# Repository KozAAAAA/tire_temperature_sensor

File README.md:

# Tire Temperature Sensor v2.0

**TTS** (Tire Temperature Sensor) is a PCB designed to measure temperature quickly, at a distance, and without the need to touch the wheels. The 4x16 pixel IR camera is used to obtain the data. It communicates with the STM microprocessor via the I2C protocol. Data is then averaged out to a 1x8 array of unsigned ints and sent with the CAN Transceiver to the car’s CAN network. This array can be then read off of the telemetry system implemented in the PM-08 racing car.

## Applications

While driving, a tire heats up. Heat dissipates differently across its surface and its rate changes depending on many factors (E.g. weather conditions or reoccurring acceleration). As a tire has its maximal temperature, exceeding this value may weaken its structural strength and cause its destruction in the worst-case scenario. This IR Camera PCB makes it possible to monitor a tire across its whole surface and prevent any damage associated with the temperature. As TTS monitors every wheel out of 4, our crew can easily detect if tires wear unevenly or excessively. Tire temperature patterns inform whether the car is properly calibrated, as the out-of-tune suspension causes tires to heat up significantly faster. This may result in grip loss in these areas.

## Core features

* 4x16 pixel MLX90621 thermal camera
* STM32L4P5RET
* 24V to 3.3V buck converter
* 3.3V to 2.6V LDO
* 3.3V CAN transceiver
* Overcurrent and reverse polarity protection
* Status LEDs

## PCB

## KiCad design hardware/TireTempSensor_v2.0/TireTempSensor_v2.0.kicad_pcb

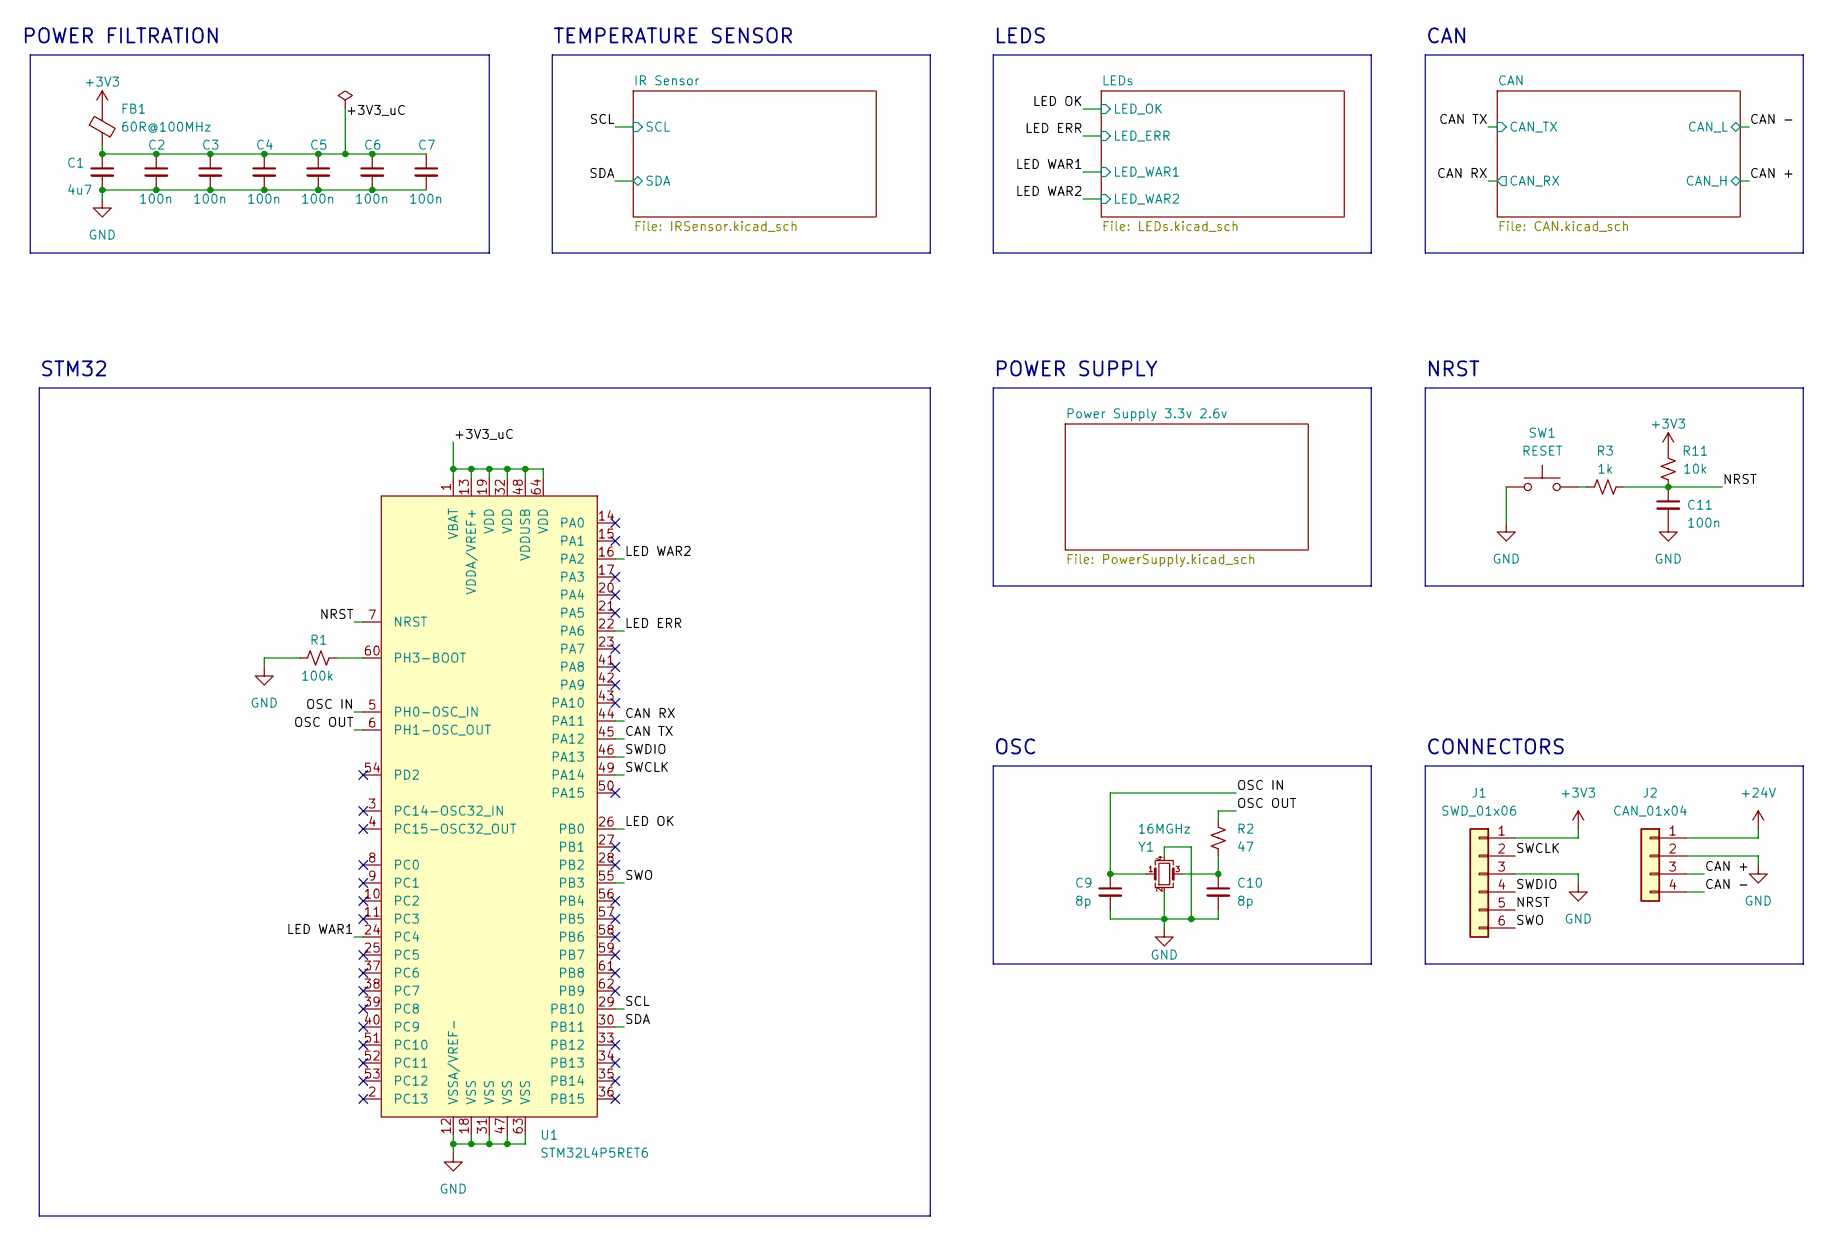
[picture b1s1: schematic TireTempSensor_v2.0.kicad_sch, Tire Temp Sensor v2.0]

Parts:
C1: 4u7; C_0603_1608Metric
C2, C3, C4, C5, C6, C7, C11: 100n; C_0603_1608Metric
C9, C10: 8p; C_0603_1608Metric
FB1: 60R@100MHz; L_0603_1608Metric
J1: SWD_01x06; PinHeader_1x06_P2.54mm_Vertical
J2: CAN_01x04; SolderWire-0.1sqmm_1x04_P3.6mm_D0.4mm_OD1mm_Relief
R1: 100k; R_0603_1608Metric
R2: 47; R_0603_1608Metric
R3: 1k; R_0603_1608Metric
R11: 10k; R_0603_1608Metric
SW1: RESET; PTS815SJK250SMTRLFS
U1: STM32L4P5RET6; LQFP-64_10x10mm_P0.5mm
Y1: 16MGHz; Crystal_SMD_SeikoEpson_TSX3225-4Pin_3.2x2.5mm

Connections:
+3V3: FB1.1, J1.1, R11.2; also elsewhere on the board
+24V: J2.1; also elsewhere on the board
/+3V3_uC: C1.1, C2.1, C3.1, C4.1, C5.1, C6.1, C7.1, FB1.2, U1.1 (VBAT), U1.13 (VDDA/VREF+), U1.19 (VDD), U1.32 (VDD), U1.48 (VDDUSB), U1.64 (VDD)
/CAN +: J2.3; also elsewhere on the board
/CAN -: J2.4; also elsewhere on the board
/CAN RX: U1.44 (PA11); also elsewhere on the board
/CAN TX: U1.45 (PA12); also elsewhere on the board
/LED ERR: U1.22 (PA6); also elsewhere on the board
/LED OK: U1.26 (PB0); also elsewhere on the board
/LED WAR1: U1.24 (PC4); also elsewhere on the board
/LED WAR2: U1.16 (PA2); also elsewhere on the board
/NRST: C11.1, J1.5, R3.2, R11.1, U1.7 (NRST)
/OSC IN: C9.1, U1.5 (PH0-OSC_IN), Y1.1
/OSC OUT: R2.1, U1.6 (PH1-OSC_OUT)
/SCL: U1.29 (PB10); also elsewhere on the board
/SDA: U1.30 (PB11); also elsewhere on the board
/SWCLK: J1.2, U1.49 (PA14)
/SWDIO: J1.4, U1.46 (PA13)
/SWO: J1.6, U1.55 (PB3)
GND: C1.2, C2.2, C3.2, C4.2, C5.2, C6.2, C7.2, C9.2, C10.2, C11.2, J1.3, J2.2, R1.2, SW1.1 (A), SW1.2 (A), U1.12 (VSSA/VREF-), U1.18 (VSS), U1.31 (VSS), U1.47 (VSS), U1.63 (VSS), Y1.2, Y1.4; also elsewhere on the board
unnamed: C10.1, R2.2, Y1.3
unnamed: R1.1, U1.60 (PH3-BOOT)
unnamed: R3.1, SW1.3 (B), SW1.4 (B)

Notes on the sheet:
NRST
POWER SUPPLY
OSC
STM32
CAN
POWER FILTRATION
LEDS
CONNECTORS
TEMPERATURE SENSOR

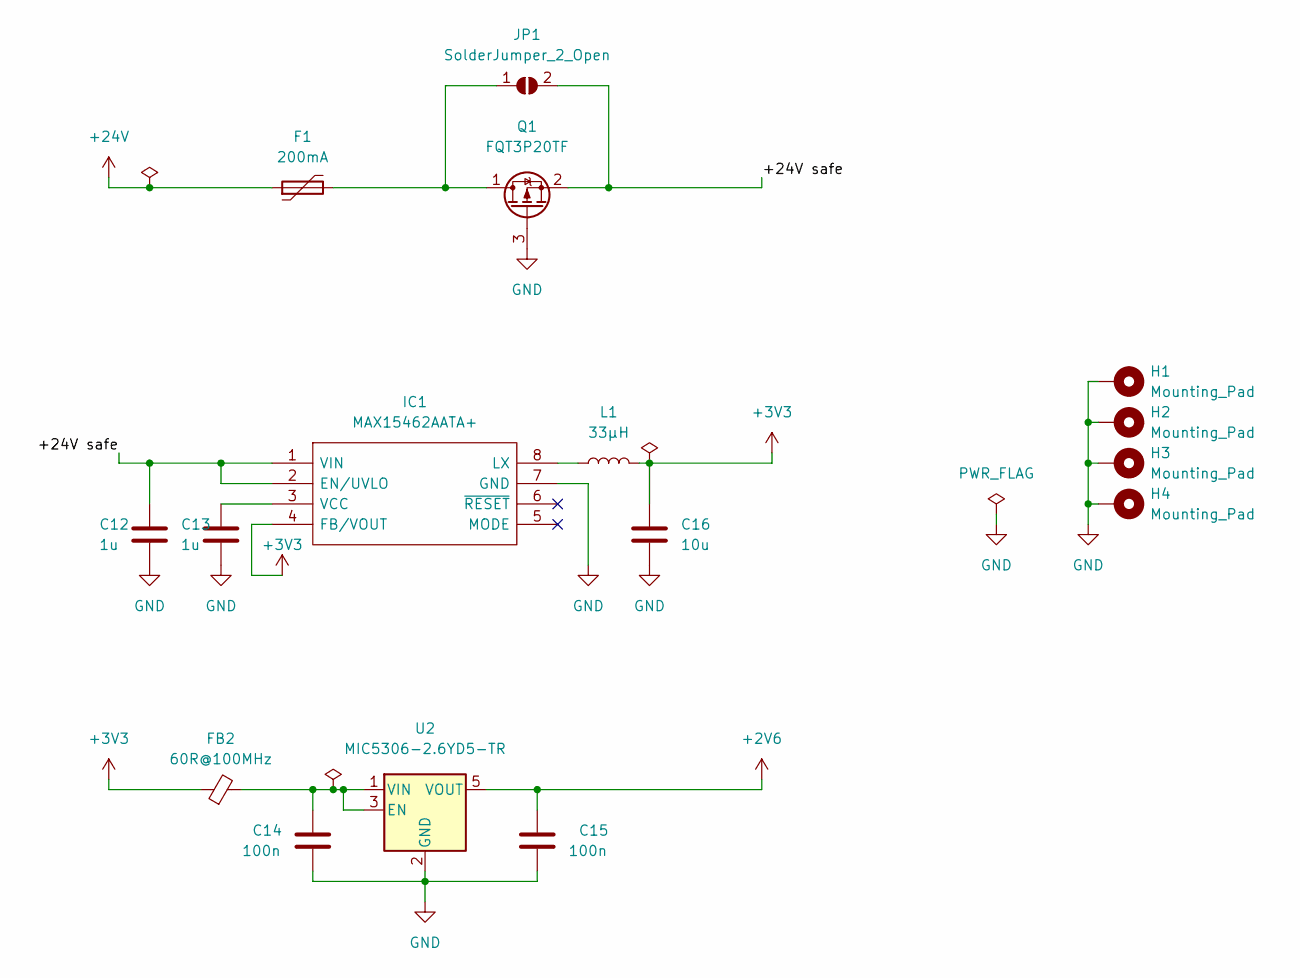
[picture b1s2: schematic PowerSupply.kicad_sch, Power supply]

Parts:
C12, C13: 1u; C_0603_1608Metric
C14, C15: 100n; C_0603_1608Metric
C16: 10u; C_1206_3216Metric
F1: 200mA; Fuse_1210_3225Metric
FB2: 60R@100MHz; L_0603_1608Metric
H1, H2, H3, H4: Mounting_Pad; MountingHole_2.7mm_M2.5_ISO14580_Pad
IC1: MAX15462AATA+; TDFN-8-1EP_2x2mm_P0.5mm_EP0.8x1.2mm; Manufacturer_Part_Number MAX15462AATA+; Mouser Part Number 700-MAX15462AATA+
JP1: SolderJumper_2_Open; SolderJumper-2_P1.3mm_Open_TrianglePad1.0x1.5mm
L1: 33μH; L_Vishay_IFSC-1515AH_4x4x1.8mm
Q1: FQT3P20TF; SOT-223-4-NFET
U2: MIC5306-2.6YD5-TR; SOT-23-5

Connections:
+2V6: C15.1, U2.5 (VOUT); also elsewhere on the board
+3V3: C16.1, FB2.1, IC1.4 (FB/VOUT), L1.2; also elsewhere on the board
+24V: F1.1; also elsewhere on the board
/Power Supply 3.3v 2.6v/+24V safe: C12.1, IC1.1 (VIN), IC1.2 (EN/UVLO), JP1.2 (B), Q1.2 (S)
GND: C12.2, C13.2, C14.2, C15.2, C16.2, H1.1, H2.1, H3.1, H4.1, IC1.7 (GND), Q1.3 (G), U2.2 (GND); also elsewhere on the board
unnamed: C13.1, IC1.3 (VCC)
unnamed: C14.1, FB2.2, U2.1 (VIN), U2.3 (EN)
unnamed: F1.2, JP1.1 (A), Q1.1 (D)
unnamed: IC1.8 (LX), L1.1

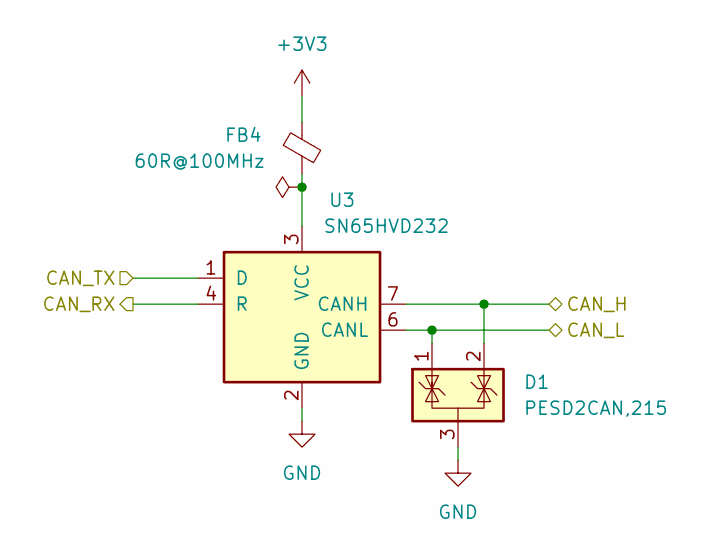
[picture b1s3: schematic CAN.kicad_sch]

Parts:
D1: PESD2CAN,215; SOT-23
FB4: 60R@100MHz; L_0603_1608Metric
U3: SN65HVD232; SOIC-8_3.9x4.9mm_P1.27mm

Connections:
+3V3: FB4.1; also elsewhere on the board
/CAN +: D1.2 (K), U3.7 (CANH); also elsewhere on the board
/CAN -: D1.1 (K), U3.6 (CANL); also elsewhere on the board
/CAN RX: U3.4 (R); also elsewhere on the board
/CAN TX: U3.1 (D); also elsewhere on the board
GND: D1.3 (A), U3.2 (GND); also elsewhere on the board
unnamed: FB4.2, U3.3 (VCC)

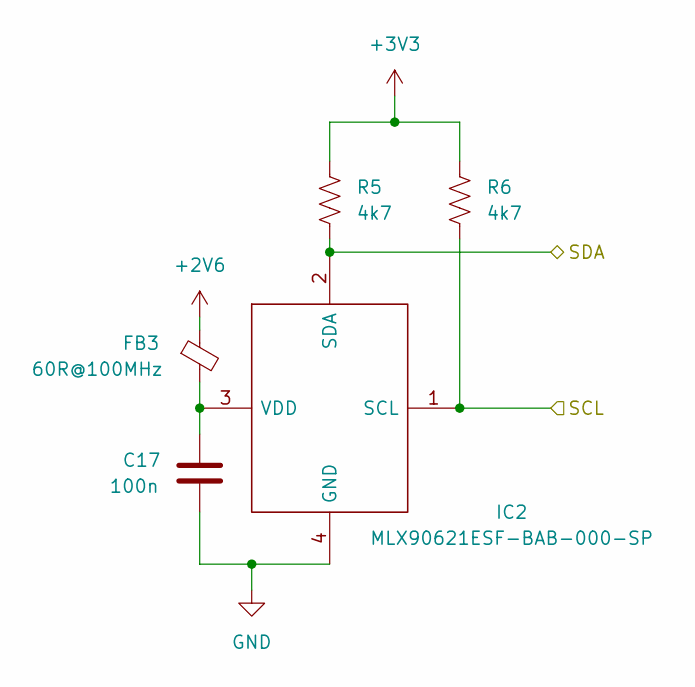
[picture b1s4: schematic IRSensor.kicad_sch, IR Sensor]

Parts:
C17: 100n; C_0603_1608Metric
FB3: 60R@100MHz; L_0603_1608Metric
IC2: MLX90621ESF-BAB-000-SP; MLX90621ESFBAB000SP; Manufacturer_Part_Number MLX90621ESF-BAB-000-SP; Mouser Part Number 482-90621ESFBAB000SP
R5, R6: 4k7; R_0603_1608Metric

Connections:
+2V6: FB3.1; also elsewhere on the board
+3V3: R5.1, R6.1; also elsewhere on the board
/SCL: IC2.1 (SCL), R6.2; also elsewhere on the board
/SDA: IC2.2 (SDA), R5.2; also elsewhere on the board
GND: C17.2, IC2.4 (GND); also elsewhere on the board
unnamed: C17.1, FB3.2, IC2.3 (VDD)

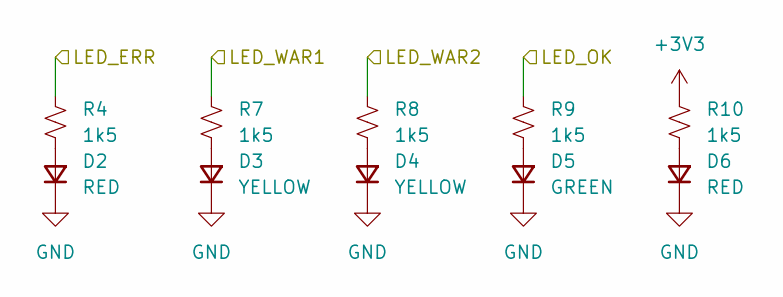
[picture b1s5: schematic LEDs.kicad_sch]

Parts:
D2, D6: RED; D_0603_1608Metric
D3, D4: YELLOW; D_0603_1608Metric
D5: GREEN; D_0603_1608Metric
R4, R7, R8, R9, R10: 1k5; R_0603_1608Metric

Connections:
+3V3: R10.1; also elsewhere on the board
/LED ERR: R4.1; also elsewhere on the board
/LED OK: R9.1; also elsewhere on the board
/LED WAR1: R7.1; also elsewhere on the board
/LED WAR2: R8.1; also elsewhere on the board
GND: D2.1 (K), D3.1 (K), D4.1 (K), D5.1 (K), D6.1 (K); also elsewhere on the board
unnamed: D2.2 (A), R4.2
unnamed: D3.2 (A), R7.2
unnamed: D4.2 (A), R8.2
unnamed: D5.2 (A), R9.2
unnamed: D6.2 (A), R10.2

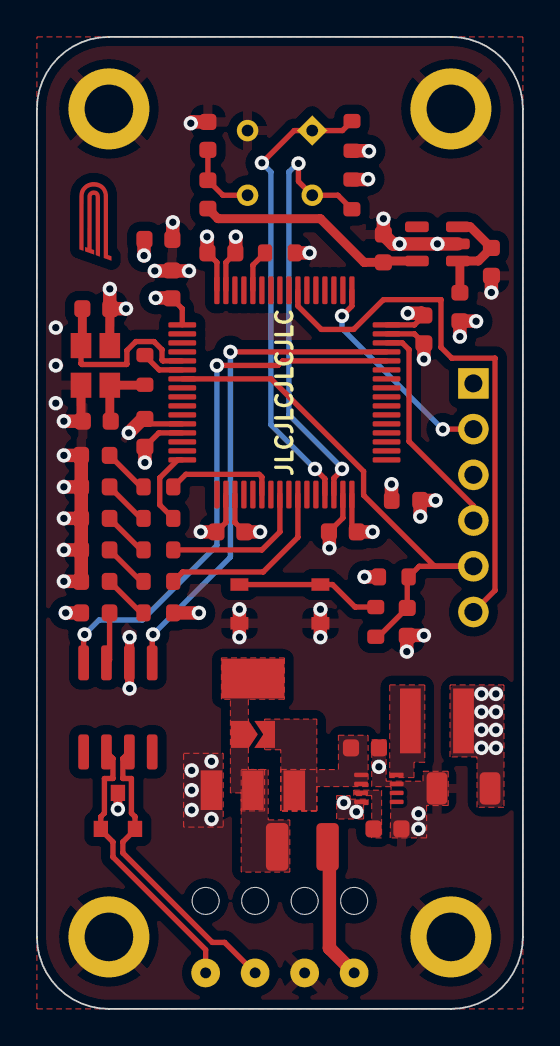
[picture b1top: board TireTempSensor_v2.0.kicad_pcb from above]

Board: 4 copper layers, 27.0 x 54.0 mm, 54 parts (1 on the bottom side), 36 nets.

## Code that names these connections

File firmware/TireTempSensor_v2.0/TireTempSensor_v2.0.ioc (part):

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Mcu.Name=STM32L4P5R(G-E)Tx
Mcu.Package=LQFP64
Mcu.UserName=STM32L4P5RETx
PA11.Mode=CAN_Activate
PA11.Signal=CAN1_RX
PA12.Mode=CAN_Activate
PA12.Signal=CAN1_TX
PA13\ (JTMS/SWDIO).Mode=Trace_Asynchronous_SW
PA13\ (JTMS/SWDIO).Signal=SYS_JTMS-SWDIO
PA14\ (JTCK/SWCLK).Mode=Trace_Asynchronous_SW
PA14\ (JTCK/SWCLK).Signal=SYS_JTCK-SWCLK
PA2.GPIOParameters=GPIO_Label
PA2.GPIO_Label=LED_WAR2
PA2.Signal=GPIO_Output
PA6.GPIOParameters=GPIO_Label
PA6.GPIO_Label=LED_ERR
PA6.Signal=GPIO_Output
PB0.GPIOParameters=GPIO_Label
PB0.GPIO_Label=LED_OK
PB0.Signal=GPIO_Output
PB10.Mode=I2C
PB10.Signal=I2C2_SCL
PB11.Mode=I2C
PB11.Signal=I2C2_SDA
PB3\ (JTDO/TRACESWO).Mode=Trace_Asynchronous_SW
PB3\ (JTDO/TRACESWO).Signal=SYS_JTDO-SWO
PC4.GPIOParameters=GPIO_Label
PC4.GPIO_Label=LED_WAR1
PC4.Signal=GPIO_Output
PH0-OSC_IN\ (PH0).Mode=HSE-External-Oscillator
PH0-OSC_IN\ (PH0).Signal=RCC_OSC_IN
PH1-OSC_OUT\ (PH1).Mode=HSE-External-Oscillator
PH1-OSC_OUT\ (PH1).Signal=RCC_OSC_OUT
RCC.HSE_VALUE=24576000
RCC.SYSCLKFreq_VALUE=98304000
RCC.SYSCLKSource=RCC_SYSCLKSOURCE_PLLCLK
board=custom

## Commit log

2022-08-15 buck & reversed bias protection
2022-08-15 PFET & buck caps models
2022-08-16 stm selection & pin assignment
2022-08-16 schematic complete
2022-08-16 erc tests passed
2022-08-16 changed the stm
2022-08-17 footprints added
2022-08-17 rough pcb layout
2022-08-18 some pcb connections
2022-08-18 more pcb connections
2022-08-18 gnd vias added
2022-08-18 connections done DRC check done
2022-08-19 silkscreen text added
2022-08-22 front silkscreen
2022-08-22 pcb is done
2022-08-22 readme
2022-08-23 reviewed
2022-08-24 ready to be ordered
2022-10-21 footprint has been changed + some minor silkscreen changes
2022-11-16 Everything tested and works - code is garbage tho
2022-12-12 3d models
2023-01-28 Restructure code
2023-01-29 Add TIM1 as main loop, Raise an error in the form of the LED color
2023-01-29 Fix bug LED OK when its not
2023-02-04 Add flags in interrupts and check them in the infinite loop
2023-02-07 Add sequential IT communication, data bug tho
2023-03-06 Add 8MHz crystal configuration
